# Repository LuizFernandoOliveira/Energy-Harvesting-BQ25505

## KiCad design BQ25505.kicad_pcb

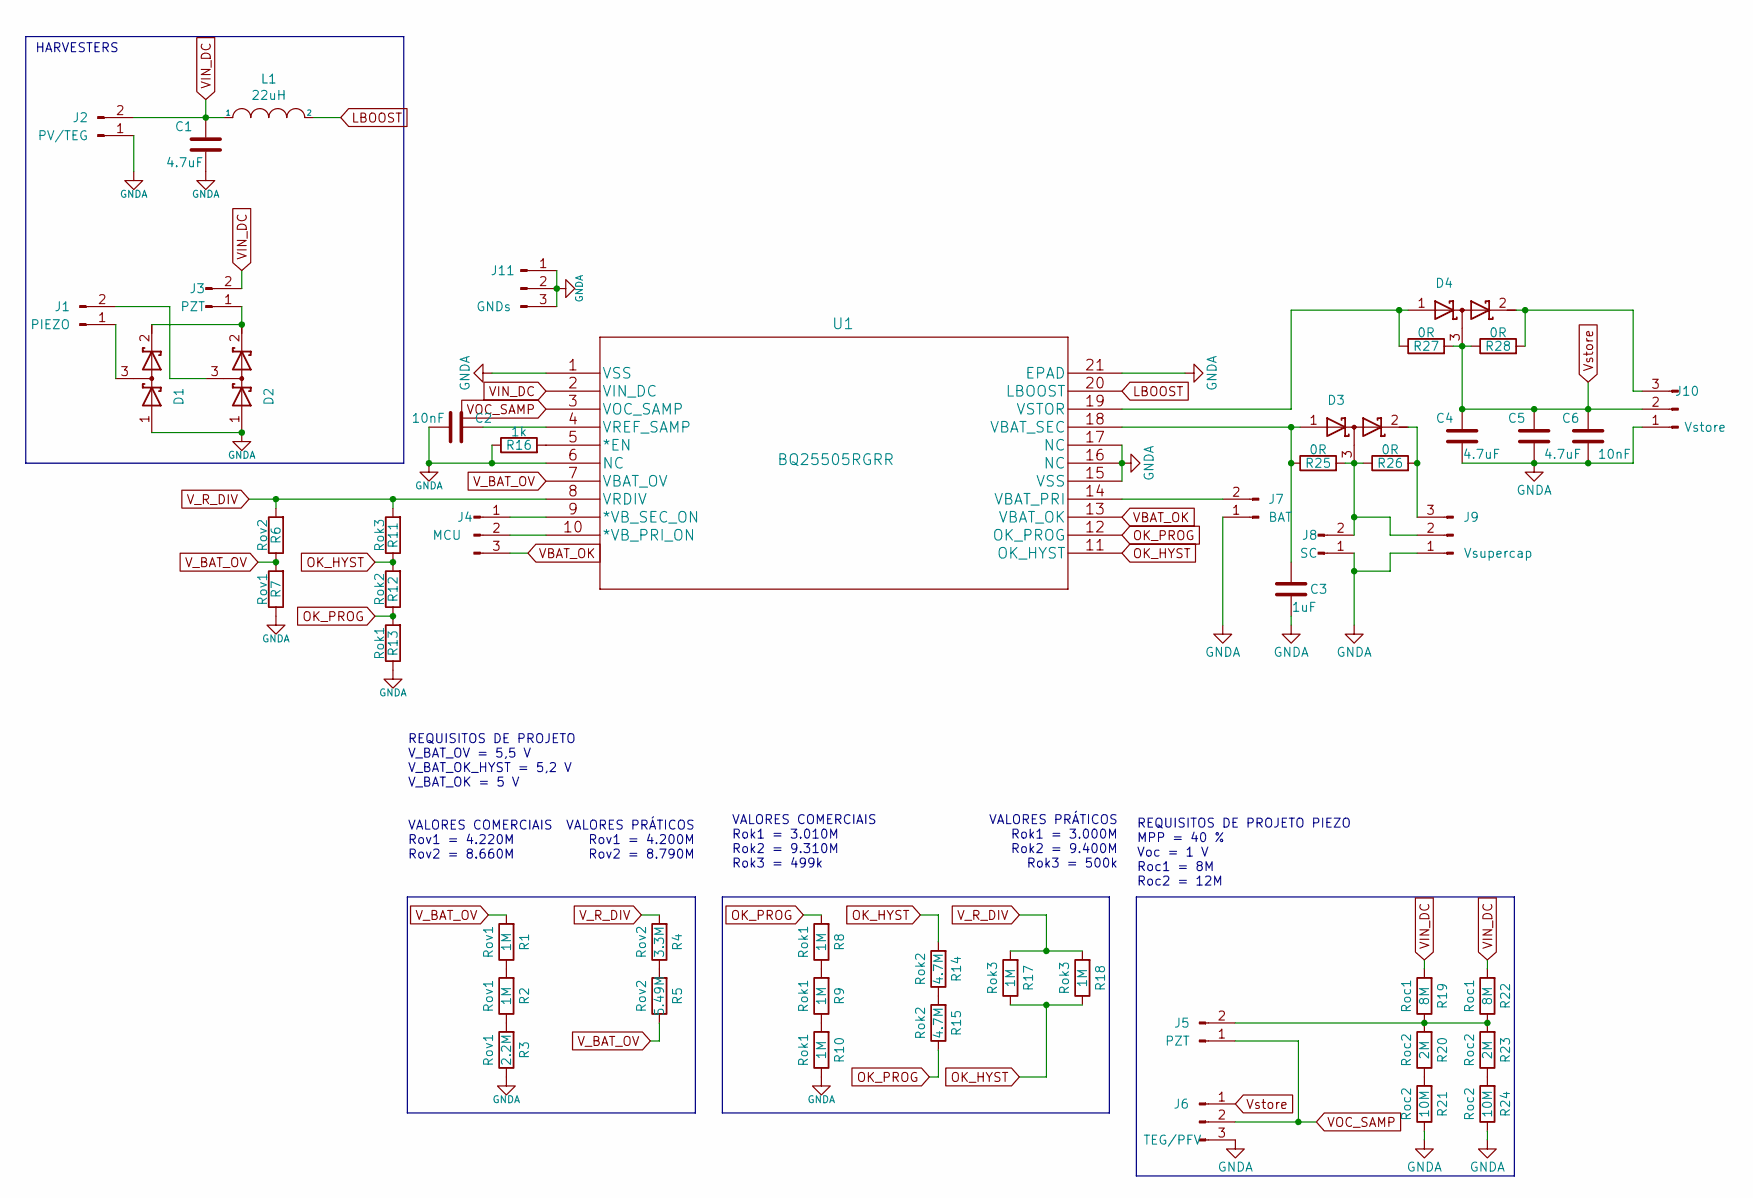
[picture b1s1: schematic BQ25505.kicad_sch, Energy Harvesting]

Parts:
C1, C4, C5: 4.7uF; C_0805_2012Metric
C2, C6: 10nF; C_0805_2012Metric
C3: 1uF; C_0805_2012Metric
D1, D2, D3, D4: D_Schottky_x2_Serial_AKC; SOT-23
J1: PIEZO; PhoenixContact_MCV_1,5_2-G-5.08_1x02_P5.08mm_Vertical
J2: PV/TEG; PhoenixContact_MCV_1,5_2-G-5.08_1x02_P5.08mm_Vertical
J3, J5: PZT; PinHeader_1x02_P2.54mm_Vertical
J4: MCU; PinHeader_1x03_P2.54mm_Vertical
J6: TEG/PFV; PinHeader_1x03_P2.54mm_Vertical
J7: BAT; PinHeader_1x02_P2.54mm_Vertical
J8: SC; PinHeader_1x02_P2.54mm_Vertical
J9: Vsupercap; PinHeader_1x03_P2.54mm_Vertical
J10: Vstore; PinHeader_1x03_P2.54mm_Vertical
J11: GNDs; PinHeader_1x03_P2.54mm_Vertical
L1: 22uH; L_0805_2012Metric_Pad1.15x1.40mm_HandSolder
R1, R2, R8, R9, R10, R17, R18: 1M; R_0805_2012Metric
R3: 2.2M; R_0805_2012Metric
R4: 3.3M; R_0805_2012Metric
R5: 5.49M; R_0603_1608Metric
R6: Rov2; R_0603_1608Metric
R7: Rov1; R_0603_1608Metric
R11: Rok3; R_0603_1608Metric
R12: Rok2; R_0603_1608Metric
R13: Rok1; R_0603_1608Metric
R14, R15: 4.7M; R_0805_2012Metric
R16: 1k; R_0805_2012Metric
R19: 8M; R_0603_1608Metric
R20: 2M; R_0603_1608Metric
R21: 10M; R_0603_1608Metric
R22: 8M; R_0805_2012Metric
R23: 2M; R_0805_2012Metric
R24: 10M; R_0805_2012Metric
R25, R26, R27, R28: 0R; R_0805_2012Metric
U1: BQ25505RGRR

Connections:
GNDA: C1.2, C2.2, C3.2, C4.2, C5.2, C6.2, D1.1 (A), D2.1 (A), J2.1, J6.3, J7.1, J8.1, J9.1, J10.1, J11.1, J11.2, J11.3, R3.1, R7.1, R10.1, R13.1, R16.1, R21.1, R24.1, U1.1 (VSS), U1.6 (NC), U1.15 (VSS), U1.16 (NC), U1.17 (NC), U1.21 (EPAD)
LBOOST: L1.2, U1.20 (LBOOST)
unnamed: C2.1, U1.4 (VREF_SAMP)
unnamed: C3.1, D3.1 (A), R25.1, U1.18 (VBAT_SEC)
unnamed: D1.2 (K), D2.2 (K), J3.1
unnamed: D1.3 (common), J1.1
unnamed: D2.3 (common), J1.2
unnamed: D3.2 (K), J9.3, R26.2
unnamed: D3.3 (common), J8.2, J9.2, R25.2, R26.1
unnamed: D4.1 (A), R27.1, U1.19 (VSTOR)
unnamed: D4.2 (K), J10.3, R28.2
unnamed: J4.1, U1.9 (*VB_SEC_ON)
unnamed: J4.2, U1.10 (*VB_PRI_ON)
unnamed: J5.2, R19.1, R20.2, R22.1, R23.2
unnamed: J7.2, U1.14 (VBAT_PRI)
unnamed: R1.1, R2.2
unnamed: R2.1, R3.2
unnamed: R4.1, R5.2
unnamed: R8.1, R9.2
unnamed: R9.1, R10.2
unnamed: R14.1, R15.2
unnamed: R16.2, U1.5 (*EN)
unnamed: R20.1, R21.2
unnamed: R23.1, R24.2
OK_HYST: R11.1, R12.2, R14.2, R17.1, R18.1, U1.11 (OK_HYST)
OK_PROG: R8.2, R12.1, R13.2, R15.1, U1.12 (OK_PROG)
VBAT_OK: J4.3, U1.13 (VBAT_OK)
VIN_DC: C1.1, J2.2, J3.2, L1.1, R19.2, R22.2, U1.2 (VIN_DC)
VOC_SAMP: J5.1, J6.2, U1.3 (VOC_SAMP)
V_BAT_OV: R1.2, R5.1, R6.1, R7.2, U1.7 (VBAT_OV)
V_R_DIV: R4.2, R6.2, R11.2, R17.2, R18.2, U1.8 (VRDIV)
Vstore: C4.1, C5.1, C6.1, D4.3 (common), J6.1, J10.2, R27.2, R28.1

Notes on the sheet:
VALORES PRÁTICOS Rov1 = 4.200M Rov2 = 8.790M
REQUISITOS DE PROJETO V_BAT_OV = 5,5 V V_BAT_OK_HYST = 5,2 V V_BAT_OK = 5 V
VALORES COMERCIAIS Rok1 = 3.010M Rok2 = 9.310M Rok3 = 499k
HARVESTERS
VALORES COMERCIAIS Rov1 = 4.220M Rov2 = 8.660M
VALORES PRÁTICOS Rok1 = 3.000M Rok2 = 9.400M Rok3 = 500k
REQUISITOS DE PROJETO PIEZO MPP = 40 % Voc = 1 V Roc1 = 8M Roc2 = 12M

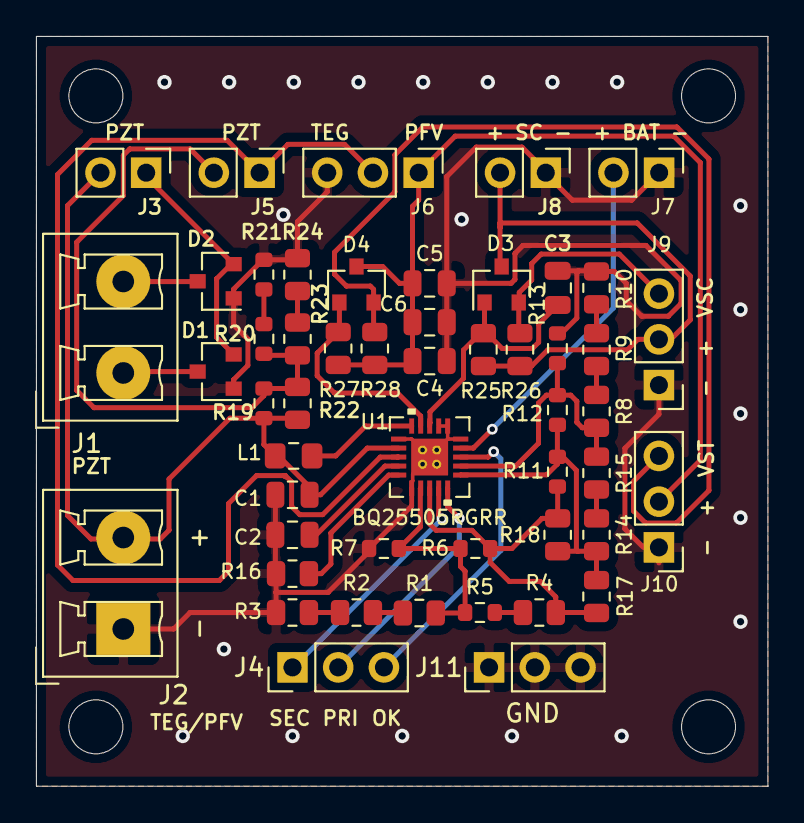
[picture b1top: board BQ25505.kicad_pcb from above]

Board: 2 copper layers, 40.6 x 41.7 mm, 51 parts (0 on the bottom side), 32 nets.
